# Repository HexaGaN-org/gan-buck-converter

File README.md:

# HexaGaN 48 V → 12 V GaN Synchronous Buck

A GaN-based synchronous buck converter with an onboard C2000 microcontroller, digital control and layered protections. HexaGaN's first in-house power PCB, built as a learning platform for the team and a rehearsal for the universal control board's power-stage interface.

> **Status (November 2026): tentative PCB layout, not ready for fabrication.** Circuitry on all six subsheets is captured and the root sheet is wired. The PCB has an outline and preliminary component placement, including XT30 input and XT60 output connectors, but placement, board-edge fit, power routing, and DRC still require substantial work. The two connectors currently overlap on the right edge and the `12V OUT` label is on the left; both need relocation and fit checks. The connector 3D models do not establish physical fit. On 2026-11-13, hierarchy ERC reported zero errors and six warnings; PCB DRC reported 770 violations and 362 unconnected items. The warnings and the [PWM overlap decision](docs/design/enable.md#open-questions) and [+5V handover margin](docs/design/input_supply.md#values-published-to-other-sheets) need review before layout freeze.

## At a glance

| | |
|---|---|
| Conversion | 48 V in → 12 V out, synchronous buck |
| Output | 12.5 A, 150 W design target; parts and copper rated for 200 W |
| Switching frequency | 400 kHz nominal, adjustable 300–500 kHz in firmware |
| Power stage | 2 × Infineon IGC033S10S1 GaN FETs, TI LM5113-Q1 gate driver |
| Controller | TI TMS320F280039C, 64-pin LQFP (same device as the universal control board) |
| Control | Staged bring-up: open loop → voltage mode → average current mode |
| Protections | Cycle-by-cycle overcurrent (CMPSS), output overvoltage, input undervoltage lockout, overtemperature, hardware enable, and static both-high PWM inhibit. Dynamic overlap protection is under review before layout freeze |
| Host interface | USB-C serial (CP2102N USB-UART bridge, ESD-protected) and a TI-compatible JTAG header |
| Assembly | JLCPCB Economic PCBA, single-sided |

Targets are in [docs/specifications.md](docs/specifications.md); each sheet's decisions and parts are in its design note in [docs/design/](docs/design/).

## Schematic sheets and owners

| # | Sheet | Owner | Status |
|---|---|---|---|
| 1 | Top (root sheet) | Reza Rahimzadeh | Wired: all six sheet symbols connected by their hierarchical pins. Four plated M3 mounting holes (H101–H104), pads on no net, a main-specifications block and a power tree |
| 2 | input_supply | Reza Rahimzadeh | Schematic complete: 48 V protection, input shunt, aux regulator, 5 V mux and 3.3 V LDO. Wired on the root sheet |
| 3 | power_stage | Reza Rahimzadeh | Captured, with reduced input and output capacitor banks (decision #24); wired on the root sheet |
| 4 | sensing | Connor Jin | Circuitry captured (six channels); labels aligned with the MCU sheet; wired on the root sheet |
| 5 | mcu | Yunxi He | Captured, with 16 MHz external crystal; all interface labels wired on the root sheet |
| 6 | enable | Connor Jin | Captured: watchdog, enable switch, `STAGE_EN` gating and static both-high inhibit. Dynamic overlap protection remains under review. Wired on the root sheet |
| 7 | comms_debug | Yunxi He | Captured: USB-C with CP2102N bridge and USBLC6 ESD protection, JTAG header. Wired on the root sheet |

The table uses each sheet's file name. On the root sheet the symbols carry display names (Input Supply, Power Stage, Sensing, Microcontroller, Enable, Comms and Debug).

Only a sheet's owner edits it. What each sheet contains and every signal that crosses between sheets are defined in [docs/schematic-hierarchy.md](docs/schematic-hierarchy.md).

## Repository layout

```
CONTRIBUTING.md              How we work: workflow, conventions, libraries, merge checklist
docs/
  specifications.md          Targets, limits and headline parts
  schematic-hierarchy.md     The contract between sheets: contents, signals, connectors
  design/                    One design note per sheet: decisions, calculations, parts, layout, tests
  guides/
    preferred-parts.md       JLCPCB passives to pick first, with measured DC-bias derating
    jlcpcb-assembly.md       Fab and assembly rules, ordering workflow, pre-order checklist
  firmware/
    firmware-requirements.md         Plain-language firmware guide for the firmware team
    edge-ai-dead-time-optimizer.md   Proposal: on-board model that picks the lowest-loss dead time and frequency
    pinmux-hardware.md              Physical MCU pin allocation frozen for PCB routing
  datasheets/                Datasheets, application notes and reference images the design notes link to
  block-diagram.svg          Board block diagram (edit the SVG directly when the architecture changes)
  gan-buck-converter-BOM.xlsx  Cost and notes per sheet, one row per unique part, rebuilt from the schematic
hardware/gan-buck-converter/
  gan-buck-converter.kicad_pro / .kicad_sch / .kicad_pcb   KiCad 10 project (root sheet and board)
  sheets/                    The six hierarchical sheets
  lib/                       hexagan library: hand-made symbols, footprints, 3D models (see lib/README.md)
  JLCImport.*                Parts imported from LCSC by the JLCImport plugin
simulations/
  voltage_mode_sim.py        Python model of the voltage-mode control loop: Bode plots, load step
  input_hotplug_sim.py       Input hot-plug ringing and damping, bulk-capacitor ripple, input-filter stability
  efficiency_estimate.py     Component loss budget and theoretical efficiency vs load, input voltage and frequency
  README.md                  How to run it, how to read the plots, what we've learned
```

Firmware source (C2000, SysConfig) will live in `firmware/` once that work starts.

## Contributing

Read [CONTRIBUTING.md](CONTRIBUTING.md) before your first commit: tool setup, the pull-and-push routine, schematic conventions, library rules and the checklist every sheet passes before it merges.

## Safety

48 V is below the 60 V DC SELV limit, but a shorted output or a failed switch can still deliver large currents and burn hardware.

- Always bring up from a **current-limited bench supply**, starting at reduced input voltage with no load.
- Connect J201 with the 48 V supply output **off**, then enable the supply. Do not routinely live-plug at 51 V until the revised input protection is measured; the controlled hot-plug test is in [input_supply.md](docs/design/input_supply.md#verification).
- Bring up the 5 V supply (through J202, the keyed external 5 V input, set to 5.0 V) before applying 48 V. J202 cuts off above about 5.2–5.7 V.
- Check polarity before connecting any electronic load or source. J201 is a male XT30 48 V input and J301 is a female XT60 12 V output; they require separate soldered adapter cables. 48 V on J301 destroys the output capacitors. See the [connector and harness instructions](docs/design/input-output-connectors.md).
- Use a 48 V supply whose **DC output floats from earth**; keep the supply's chassis protective earth connected. Set supply OVP near 55 V if available. Above about 57 V the input TVS conducts continuously.
- **Q201 grounding rule:** J201− is separate from board `GND`. Attach grounded scope clips only to board `GND`, never J201−. If both supply negative and board `GND` are earthed, USB/JTAG/scope wiring can carry input return current around Q201 during normal operation. Swapping the input leads alone does not create that bypass, but a fixed J201−-to-GND short defeats the reverse block. H101–H104 are plated but on no net: never connect them to `GND` or any other net, and keep other copper clear of their mounting hardware.
- **Grounded-scope design limit:** Moving reverse protection to the positive rail alone does not eliminate the supply/scope earth loop. If J201− were then tied directly to board `GND`, reversed leads with a grounded scope attached could short supply positive to earth outside F201. Use the [grounding and scope note](docs/design/input_supply.md#grounding-and-scope-measurements) before changing this topology or using a shared-ground source.
- The power stage stays disabled until the hardware enable is asserted. Firmware alone cannot enable it.

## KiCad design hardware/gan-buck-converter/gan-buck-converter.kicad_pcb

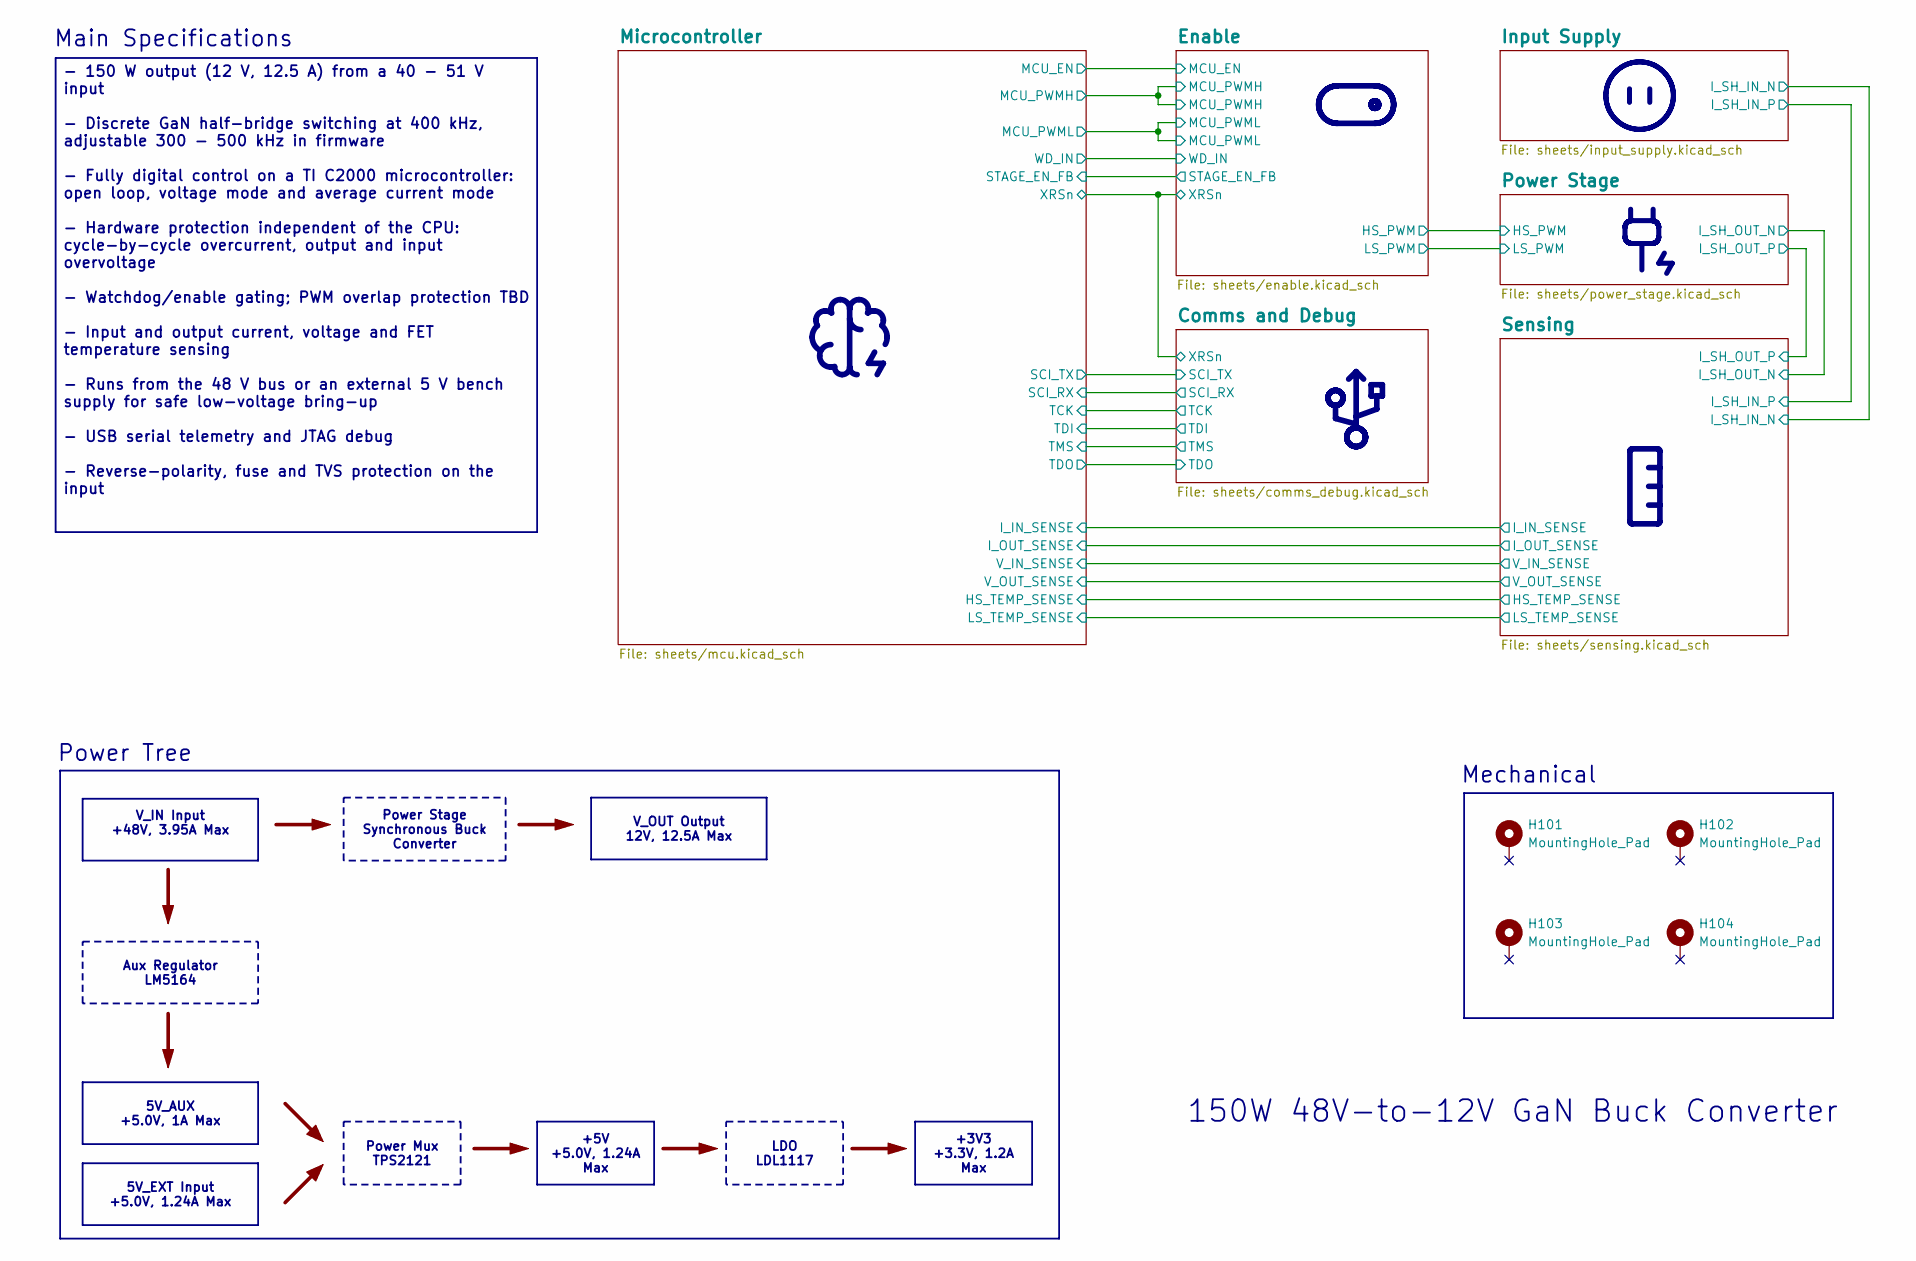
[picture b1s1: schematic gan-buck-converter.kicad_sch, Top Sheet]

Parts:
H101, H102, H103, H104: MountingHole_Pad; MountingHole_3.2mm_M3_Pad

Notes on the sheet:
Main Specifications
150W 48V-to-12V GaN Buck Converter
Power Tree
Mechanical
+3V3 +3.3V, 1.2A Max
- 150 W output (12 V, 12.5 A) from a 40 - 51 V input - Discrete GaN half-bridge switching at 400 kHz, adjustable 300 - 500 kHz in firmware - Fully digital control on a TI C2000 microcontroller: open loop, voltage mode and average current mode - Hardware protection independent of the CPU: cycle-by-c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
Power Mux TPS2121
V_OUT Output 12V, 12.5A Max
Power Stage Synchronous Buck Converter
V_IN Input +48V, 3.95A Max
Aux Regulator LM5164
5V_EXT Input +5.0V, 1.24A Max
LDO LDL1117
5V_AUX +5.0V, 1A Max
+5V +5.0V, 1.24A Max

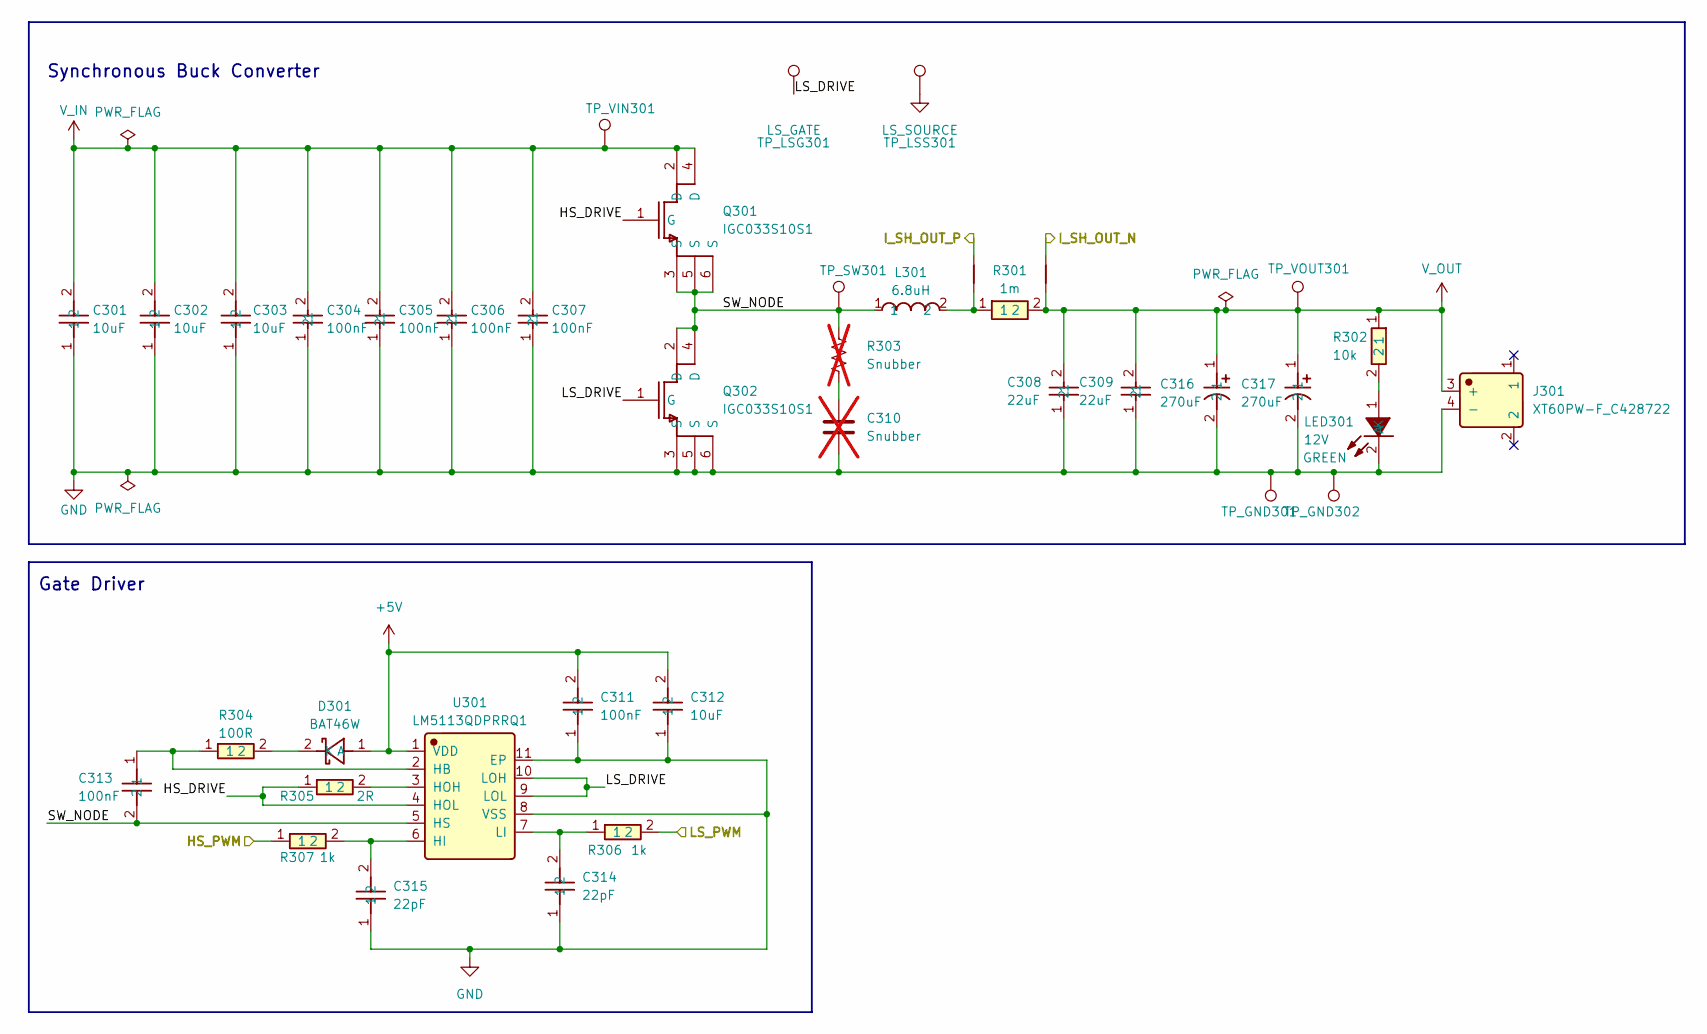
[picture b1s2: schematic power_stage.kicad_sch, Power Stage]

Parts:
C301, C302, C303: 10uF; C_1210_3225Metric; Manufacturer Part CL32Y106KCV6PNE; LCSC C22380050
C304, C305, C306, C307: 100nF; C_0603_1608Metric; Manufacturer Part CL10B104KC8NNNC; LCSC C15725
C308, C309: 22uF; C_1206_3216Metric_Pad1.33x1.80mm_HandSolder; Manufacturer Part CL31A226KAHNNNE; LCSC C12891
C310: Snubber; C_1206_3216Metric; not fitted
C311, C313: 100nF; CC0603KRX7R9BB104; Manufacturer Part CC0603KRX7R9BB104; LCSC C14663
C312: 10uF; CL10A106MA8NRNC; Manufacturer Part CL10A106MA8NRNC; LCSC C96446
C314, C315: 22pF; CL10C220JB8NNNC; Manufacturer Part CL10C220JB8NNNC; LCSC C1653
C316, C317: 270uF; APXJ160ARA271MF80J; Manufacturer Part APXJ160ARA271MF80J; LCSC C2944013
D301: BAT46W; BAT46W_C7420332; Manufacturer Part BAT46W; LCSC C7420332
J301: XT60PW-F_C428722; Manufacturer Part XT60PW-F; LCSC C428722
L301: 6.8uH; SLB2212P6R8MTT; Manufacturer Part SLB2212P6R8MTT; LCSC C2842794
LED301: 12V; 0805G_Green; Manufacturer Part KT-0805G; LCSC C2297
NT301, NT302: NetTie_2; NetTie-2_SMD_Pad0.5mm
Q301, Q302: IGC033S10S1; IGC033S10S1_C41381300; Manufacturer Part IGC033S10S1; LCSC C41381300
R301: 1m; R_2512_6332Metric_Pad1.40x3.35mm_HandSolder; Manufacturer Part FPM253WFR001TML; LCSC C7420016
R302: 10k; 0603WAF1002T5E; Manufacturer Part 0603WAF1002T5E; LCSC C25804
R303: Snubber; R_1206_3216Metric; not fitted
R304: 100R; 0603WAF1000T5E; Manufacturer Part 0603WAF1000T5E; LCSC C22775
R305: 2R; 0603WAF200KT5E; Manufacturer Part 0603WAF200KT5E; LCSC C22977
R306, R307: 1k; 0603WAF1001T5E; Manufacturer Part 0603WAF1001T5E; LCSC C21190
TP_GND301, TP_GND302: TestPoint; TestPoint_Pad_D2.0mm
TP_LSG301: LS_GATE; TestPoint_Pad_D1.0mm
TP_LSS301: LS_SOURCE; TestPoint_Pad_D1.0mm
TP_SW301: TestPoint; TestPoint_Pad_D2.0mm
TP_VIN301: TestPoint; TestPoint_Pad_D2.0mm
TP_VOUT301: TestPoint; TestPoint_Pad_D2.0mm
U301: LM5113QDPRRQ1; Manufacturer Part LM5113QDPRRQ1; LCSC C2677036

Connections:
+5V: C311.2, C312.2, D301.1 (A), U301.1 (VDD); also elsewhere on the board
/Enable/HS_PWM: R307.1; also elsewhere on the board
/Enable/LS_PWM: R306.2; also elsewhere on the board
/Power Stage/HS_DRIVE: Q301.1 (G), R305.1, U301.4 (HOL)
/Power Stage/I_SH_OUT_N: NT302.2; also elsewhere on the board
/Power Stage/I_SH_OUT_P: NT301.2; also elsewhere on the board
/Power Stage/LS_DRIVE: Q302.1 (G), TP_LSG301.1 (1_1), U301.9 (LOL), U301.10 (LOH)
/Power Stage/SW_NODE: C313.2, L301.1, Q301.3 (S), Q301.5 (S), Q301.6 (S), Q302.2 (D), Q302.4 (D), R303.1, TP_SW301.1 (1_1), U301.5 (HS)
GND: C301.1, C302.1, C303.1, C304.1, C305.1, C306.1, C307.1, C308.1, C309.1, C310.2, C311.1, C312.1, C314.1, C315.1, C316.2, C317.2, J301.4 (-), LED301.2 (K), Q302.3 (S), Q302.5 (S), Q302.6 (S), TP_GND301.1 (1_1), TP_GND302.1 (1_1), TP_LSS301.1 (1_1), U301.8 (VSS), U301.11 (EP); also elsewhere on the board
unnamed: C310.1, R303.2
unnamed: D301.2 (K), R304.2
unnamed: L301.2, NT301.1, R301.1
unnamed: LED301.1 (A), R302.2
unnamed: C313.1, R304.1, U301.2 (HB)
unnamed: C315.2, R307.2, U301.6 (HI)
unnamed: R305.2, U301.3 (HOH)
unnamed: C314.2, R306.1, U301.7 (LI)
V_IN: C301.2, C302.2, C303.2, C304.2, C305.2, C306.2, C307.2, Q301.2 (D), Q301.4 (D), TP_VIN301.1 (1_1); also elsewhere on the board
V_OUT: C308.2, C309.2, C316.1, C317.1, J301.3 (+), NT302.1, R301.2, R302.1, TP_VOUT301.1 (1_1); also elsewhere on the board

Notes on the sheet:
Synchronous Buck Converter
Gate Driver

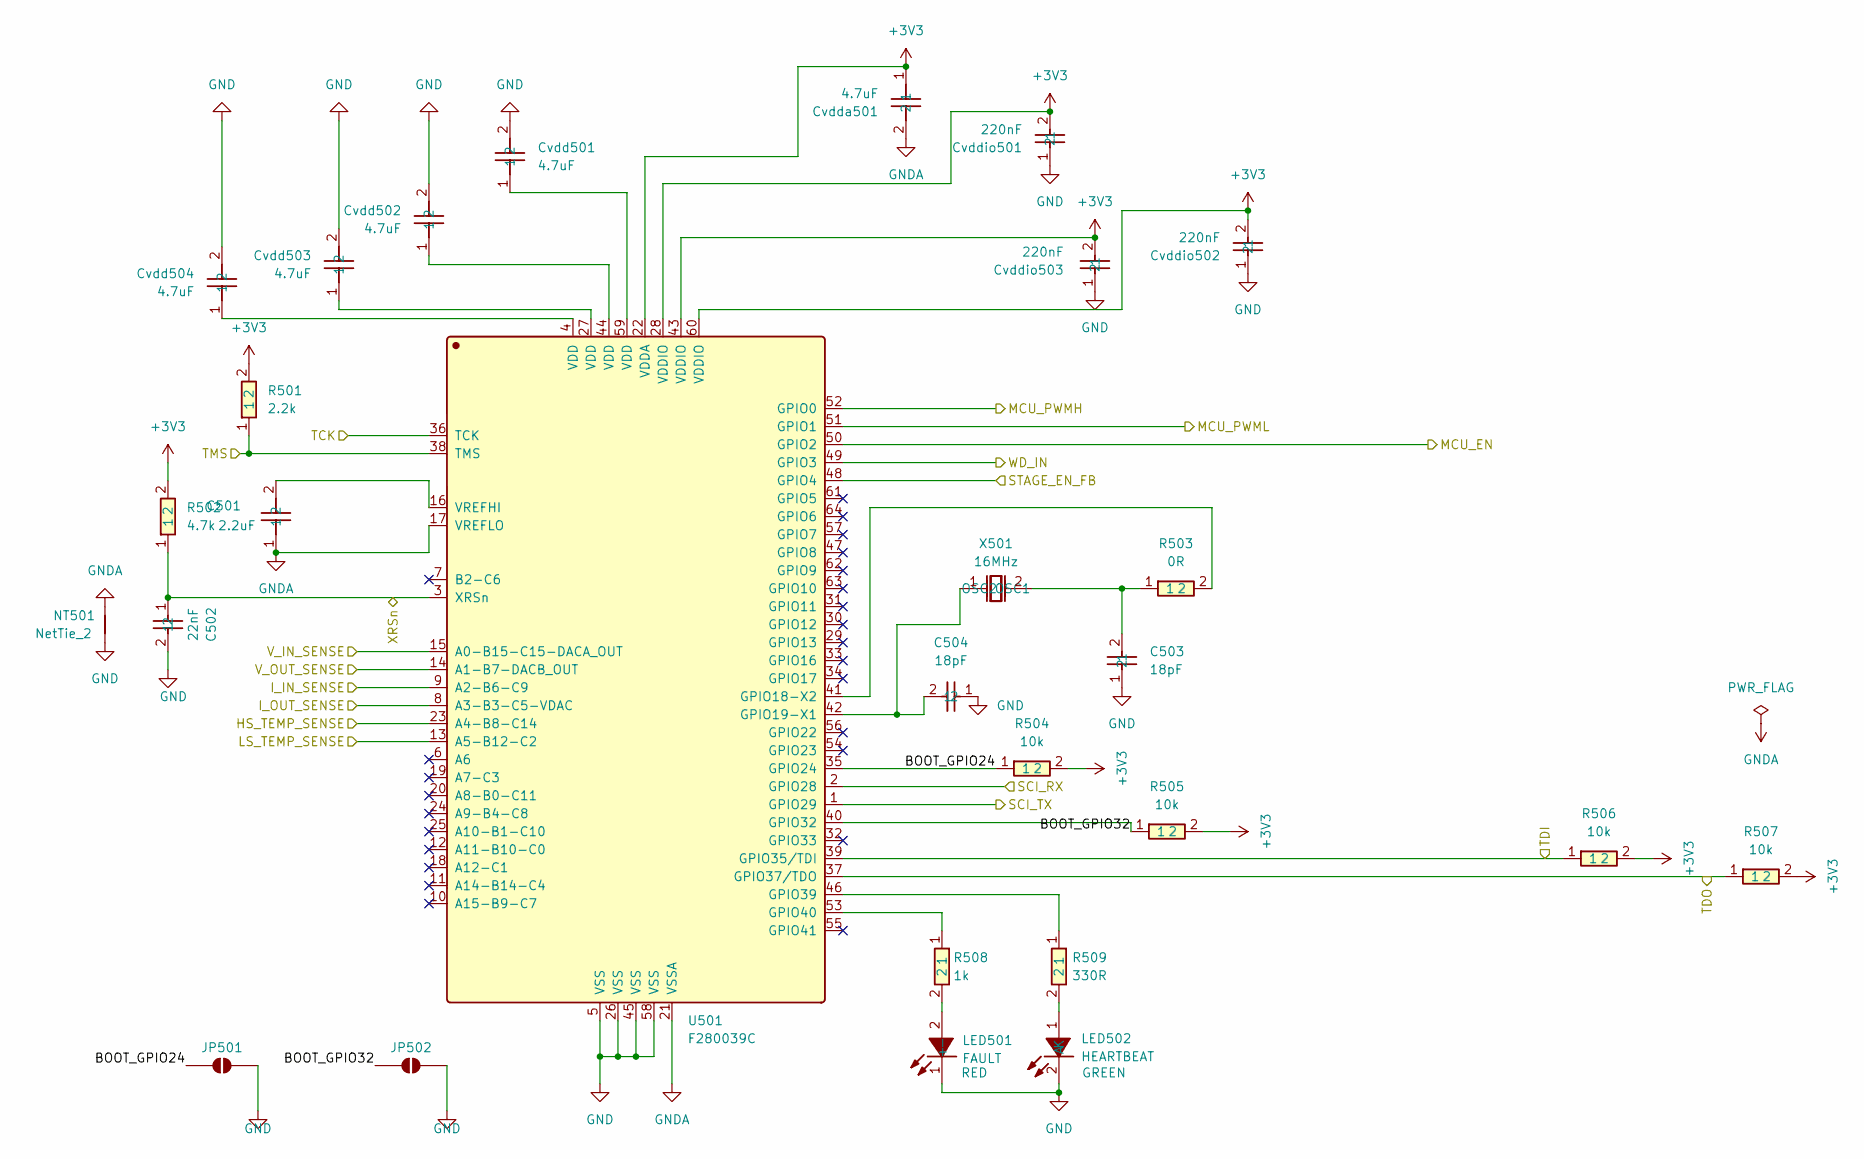
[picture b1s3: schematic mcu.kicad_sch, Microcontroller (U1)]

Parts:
C501: 2.2uF; GRM188R71A225KE15D; Manufacturer Part GRM188R71A225KE15D; LCSC C86018
C502: 22nF; CL10B223KB8NNNC; Manufacturer Part CL10B223KB8NNNC; LCSC C21122
C503, C504: 18pF; CL10C180JB8NNNC; Manufacturer Part CL10C180JB8NNNC; LCSC C1647
Cvdd501, Cvdd502, Cvdd503, Cvdd504: 4.7uF; CL10B475KQ8NQNC; Manufacturer Part CL10B475KQ8NQNC; LCSC C107368
Cvdda501: 4.7uF; CL10B475KQ8NQNC; Manufacturer Part CL10B475KQ8NQNC; LCSC C107368
Cvddio501, Cvddio502, Cvddio503: 220nF; CL10B224KA8NNNC; Manufacturer Part CL10B224KA8NNNC; LCSC C21120
JP501: BOOT_GPIO24; SolderJumper-2_P1.3mm_Open_Pad1.0x1.5mm
JP502: BOOT_GPIO32; SolderJumper-2_P1.3mm_Open_Pad1.0x1.5mm
LED501: FAULT; FC-2012HRK-620D; Manufacturer Part NCD0805R1; LCSC C84256
LED502: HEARTBEAT; 0805G_Green; Manufacturer Part KT-0805G; LCSC C2297
NT501: NetTie_2; NetTie-2_SMD_Pad0.5mm
R501: 2.2k; 0603WAF2201T5E; Manufacturer Part 0603WAF2201T5E; LCSC C4190
R502: 4.7k; RCT034K7JLF; Manufacturer Part RCT034K7JLF; LCSC C177333
R503: 0R; 0603WAJ0000T5E; Manufacturer Part 0603WAJ0000T5E; LCSC C15402
R504, R505, R506, R507: 10k; RCT0310KJLF; Manufacturer Part RCT0310KJLF; LCSC C177337
R508: 1k; 0603WAF1001T5E; Manufacturer Part 0603WAF1001T5E; LCSC C21190
R509: 330R; 0603WAF3300T5E; Manufacturer Part 0603WAF3300T5E; LCSC C23138
U501: F280039C; F280039CSPM; Manufacturer Part F280039CSPMR; LCSC C20345419
X501: 16MHz; ESD16_0000F12M25F; Manufacturer Part ESD16.0000F12M25F; LCSC C353726

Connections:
+3V3: Cvdda501.1, Cvddio501.2, Cvddio502.2, Cvddio503.2, R501.2, R502.2, R504.2, R505.2, R506.2, R507.2, U501.22 (VDDA), U501.28 (VDDIO), U501.43 (VDDIO), U501.60 (VDDIO); also elsewhere on the board
/Comms and Debug/SCI_RX: U501.2 (GPIO28); also elsewhere on the board
/Comms and Debug/SCI_TX: U501.1 (GPIO29); also elsewhere on the board
/Comms and Debug/TCK: U501.36 (TCK); also elsewhere on the board
/Comms and Debug/TDI: R506.1, U501.39 (GPIO35/TDI); also elsewhere on the board
/Comms and Debug/TDO: R507.1, U501.37 (GPIO37/TDO); also elsewhere on the board
/Comms and Debug/TMS: R501.1, U501.38 (TMS); also elsewhere on the board
/Comms and Debug/XRSn: C502.1, R502.1, U501.3 (XRSn); also elsewhere on the board
/Enable/MCU_EN: U501.50 (GPIO2); also elsewhere on the board
/Enable/MCU_PWMH: U501.52 (GPIO0); also elsewhere on the board
/Enable/MCU_PWML: U501.51 (GPIO1); also elsewhere on the board
/Enable/STAGE_EN_FB: U501.48 (GPIO4); also elsewhere on the board
/Enable/WD_IN: U501.49 (GPIO3); also elsewhere on the board
/Microcontroller/BOOT_GPIO24: JP501.1 (A), R504.1, U501.35 (GPIO24)
/Microcontroller/BOOT_GPIO32: JP502.1 (A), R505.1, U501.40 (GPIO32)
/Microcontroller/HS_TEMP_SENSE: U501.23 (A4-B8-C14); also elsewhere on the board
/Microcontroller/I_IN_SENSE: U501.9 (A2-B6-C9); also elsewhere on the board
/Microcontroller/I_OUT_SENSE: U501.8 (A3-B3-C5-VDAC); also elsewhere on the board
/Microcontroller/LS_TEMP_SENSE: U501.13 (A5-B12-C2); also elsewhere on the board
/Microcontroller/V_IN_SENSE: U501.15 (A0-B15-C15-DACA_OUT); also elsewhere on the board
/Microcontroller/V_OUT_SENSE: U501.14 (A1-B7-DACB_OUT); also elsewhere on the board
GND: C502.2, C503.1, C504.1, Cvdd501.2, Cvdd502.2, Cvdd503.2, Cvdd504.2, Cvddio501.1, Cvddio502.1, Cvddio503.1, JP501.2 (B), JP502.2 (B), LED501.1 (-), LED502.2 (K), NT501.1, U501.5 (VSS), U501.26 (VSS), U501.45 (VSS), U501.58 (VSS); also elsewhere on the board
GNDA: C501.1, Cvdda501.2, NT501.2, U501.17 (VREFLO), U501.21 (VSSA); also elsewhere on the board
unnamed: Cvdd501.1, U501.59 (VDD)
unnamed: Cvdd502.1, U501.44 (VDD)
unnamed: Cvdd503.1, U501.27 (VDD)
unnamed: Cvdd504.1, U501.4 (VDD)
unnamed: LED501.2 (+), R508.2
unnamed: LED502.1 (A), R509.2
unnamed: R503.2, U501.41 (GPIO18-X2)
unnamed: C504.2, U501.42 (GPIO19-X1), X501.1 (OSC1)
unnamed: R509.1, U501.46 (GPIO39)
unnamed: R508.1, U501.53 (GPIO40)
unnamed: C501.2, U501.16 (VREFHI)
unnamed: C503.2, R503.1, X501.2 (OSC2)

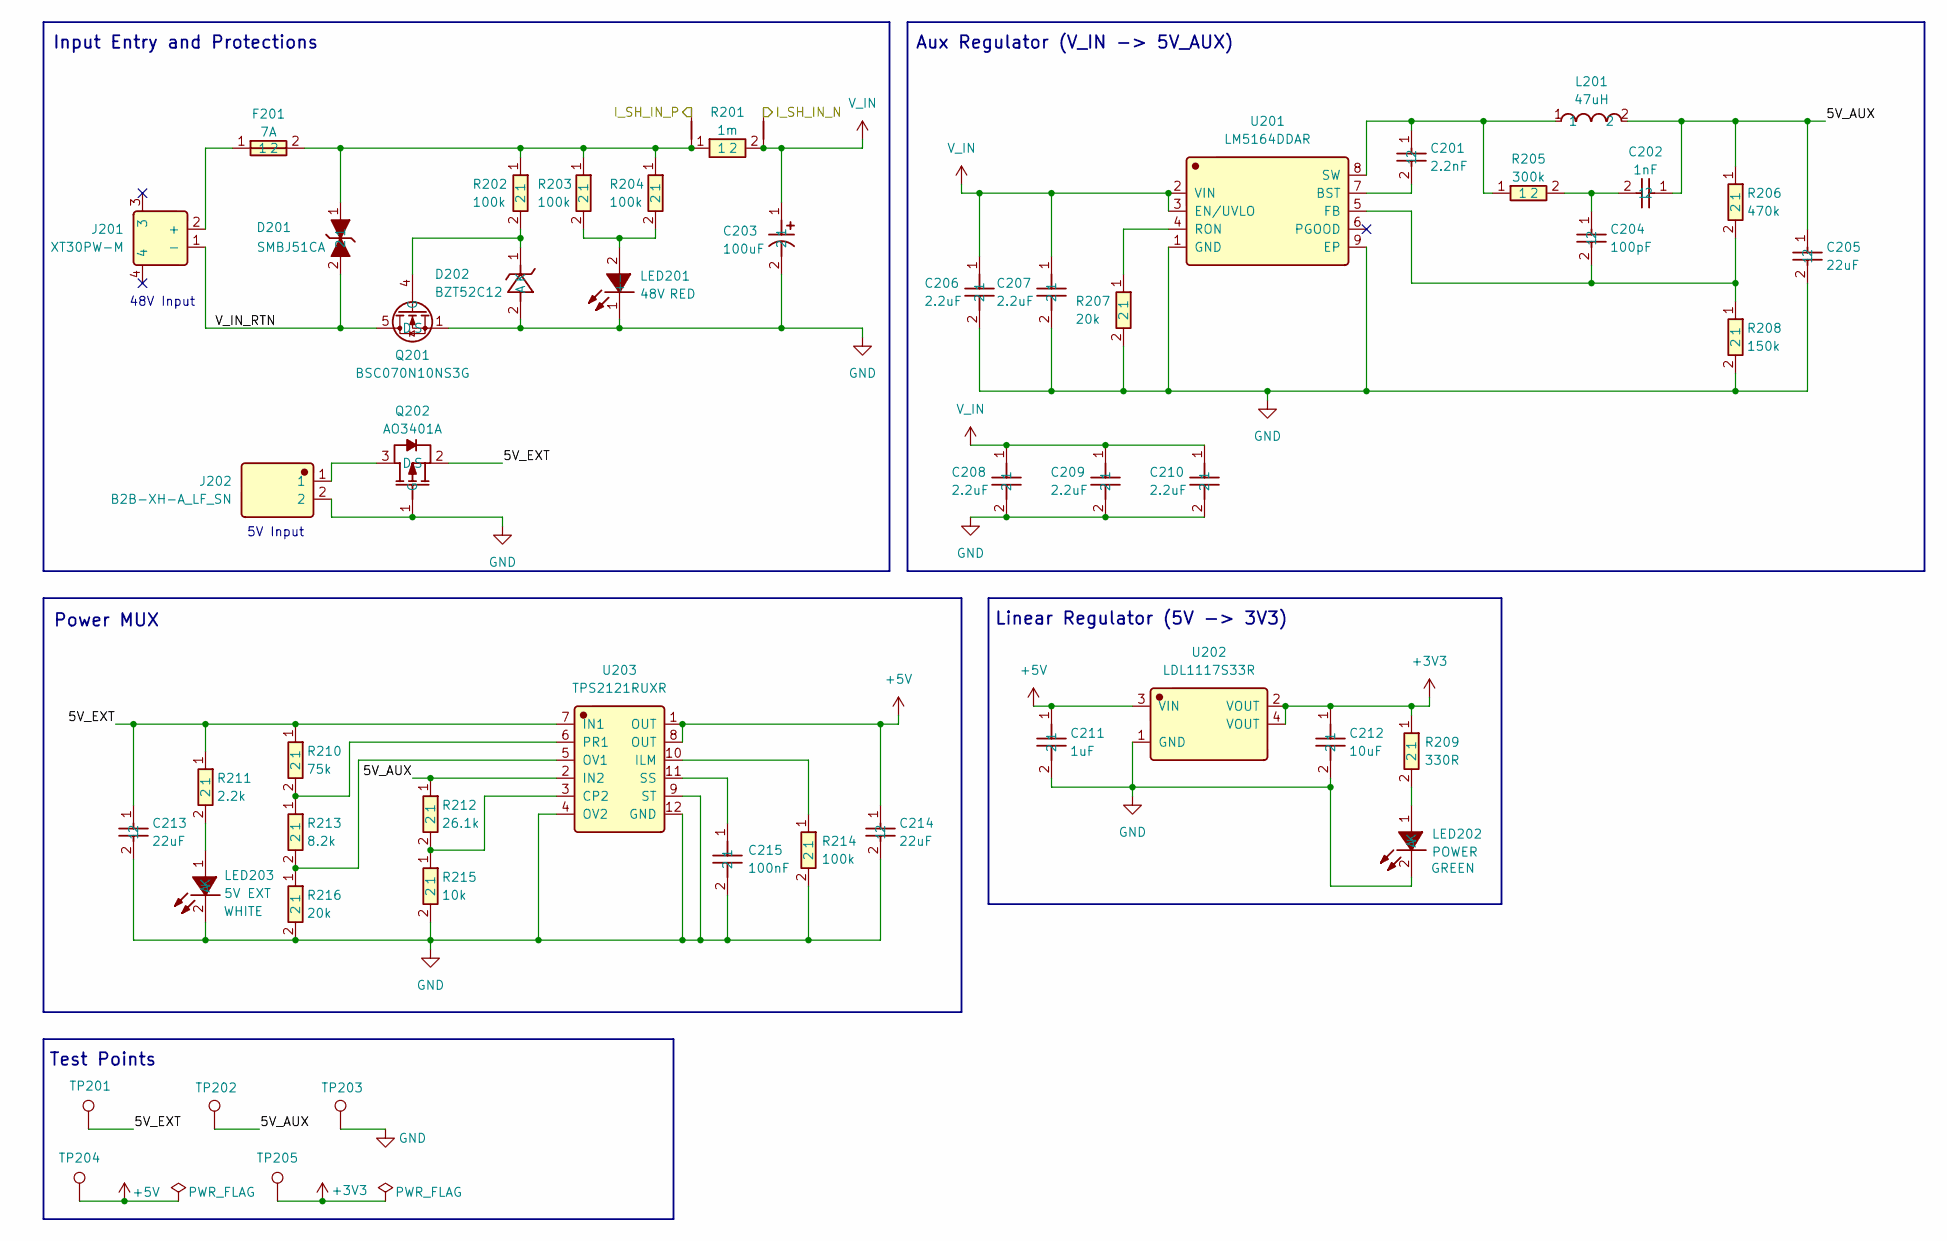
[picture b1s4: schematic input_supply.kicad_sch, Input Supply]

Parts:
C201: 2.2nF; 0603B222K500NT; Manufacturer Part 0603B222K500NT; LCSC C1604
C202: 1nF; CL10B102KB8NNNC; Manufacturer Part CL10B102KB8NNNC; LCSC C1588
C203: 100uF; VKME1452A101MV; Manufacturer Part VKME1452A101MV; LCSC C487440
C204: 100pF; CL10C101JB8NNNC; Manufacturer Part CL10C101JB8NNNC; LCSC C14858
C205, C213, C214: 22uF; C_1206_3216Metric_Pad1.33x1.80mm_HandSolder; Manufacturer Part CL31A226KAHNNNE; LCSC C12891
C206, C207, C208, C209, C210: 2.2uF; C_1206_3216Metric_Pad1.33x1.80mm_HandSolder; Manufacturer Part CL31B225KCHSNNE; LCSC C170101
C211: 1uF; CL10A105KB8NNNC; Manufacturer Part CL10A105KB8NNNC; LCSC C15849
C212: 10uF; CL10A106MA8NRNC; Manufacturer Part CL10A106MA8NRNC; LCSC C96446
C215: 100nF; CC0603KRX7R9BB104; Manufacturer Part CC0603KRX7R9BB104; LCSC C14663
D201: SMBJ51CA; SMBJ51CA_C41376101; Manufacturer Part SMBJ51CA; LCSC C41376101
D202: BZT52C12; D_SOD-123; Manufacturer Part BZT52C12; LCSC C19077410
F201: 7A; 0451007_MRL; Manufacturer Part 0451007.MRL; LCSC C99548
J201: XT30PW-M; Manufacturer Part XT30PW-M30.G.Y; LCSC C431092
J202: B2B-XH-A_LF_SN; Manufacturer Part B2B-XH-A(LF)(SN); LCSC C158012
L201: 47uH; FNR8040S470MT; Manufacturer Part FNR8040S470MT; LCSC C168137
LED201: 48V; FC-2012HRK-620D; Manufacturer Part NCD0805R1; LCSC C84256
LED202: POWER; 0805G_Green; Manufacturer Part KT-0805G; LCSC C2297
LED203: 5V EXT; whiteLEDSMD; Manufacturer Part KT-0805W; LCSC C34499
NT201, NT202: NetTie_2; NetTie-2_SMD_Pad0.5mm
Q201: BSC070N10NS3G; Manufacturer Part BSC070N10NS3G; LCSC C501502
Q202: AO3401A; Manufacturer Part AO3401A; LCSC C15127
R201: 1m; R_2512_6332Metric_Pad1.40x3.35mm_HandSolder; Manufacturer Part FPM253WFR001TML; LCSC C7420016
R202, R203, R204: 100k; R_1206_3216Metric; Manufacturer Part 1206W4F1003T5E; LCSC C17900
R205: 300k; R_0805_2012Metric_Pad1.20x1.40mm_HandSolder; Manufacturer Part 0805W8F3003T5E; LCSC C17616
R206: 470k; 0603WAF4703T5E; Manufacturer Part 0603WAF4703T5E; LCSC C23178
R207, R216: 20k; 0603WAF2002T5E; Manufacturer Part 0603WAF2002T5E; LCSC C4184
R208: 150k; 0603WAF1503T5E; Manufacturer Part 0603WAF1503T5E; LCSC C22807
R209: 330R; 0603WAF3300T5E; Manufacturer Part 0603WAF3300T5E; LCSC C23138
R210: 75k; 0603WAF7502T5E; Manufacturer Part 0603WAF7502T5E; LCSC C23242
R211: 2.2k; 0603WAF2201T5E; Manufacturer Part 0603WAF2201T5E; LCSC C4190
R212: 26.1k; 0603WAF2612T5E; Manufacturer Part 0603WAF2612T5E; LCSC C23356
R213: 8.2k; 0603WAF8201T5E; Manufacturer Part 0603WAF8201T5E; LCSC C25981
R214: 100k; 0603WAF1003T5E; Manufacturer Part 0603WAF1003T5E; LCSC C25803
R215: 10k; 0603WAF1002T5E; Manufacturer Part 0603WAF1002T5E; LCSC C25804
TP201: 5V_EXT; TestPoint_Pad_D2.0mm
TP202: 5V_AUX; TestPoint_Pad_D2.0mm
TP203: GND; TestPoint_Pad_D2.0mm
TP204: 5V; TestPoint_Pad_D2.0mm
TP205: 3V3; TestPoint_Pad_D2.0mm
U201: LM5164DDAR; Manufacturer Part LM5164DDAR; LCSC C477928
U202: LDL1117S33R; Manufacturer Part LDL1117S33R; LCSC C435835
U203: TPS2121RUXR; Texas_VQFN-HR-12_2x2.5mm_P0.5mm; Manufacturer Part TPS2121RUXR; LCSC C485916

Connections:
+3V3: C212.1, R209.1, TP205.1 (1_1), U202.2 (VOUT), U202.4 (VOUT); also elsewhere on the board
+5V: C211.1, C214.1, TP204.1 (1_1), U202.3 (VIN), U203.1 (OUT), U203.8 (OUT); also elsewhere on the board
/Input Supply/5V_AUX: C202.1, C205.1, L201.2, R206.1, R212.1, TP202.1 (1_1), U203.2 (IN2)
/Input Supply/5V_EXT: C213.1, Q202.2 (S), R210.1, R211.1, TP201.1 (1_1), U203.7 (IN1)
/Input Supply/I_SH_IN_N: NT202.2; also elsewhere on the board
/Input Supply/I_SH_IN_P: NT201.2; also elsewhere on the board
/Input Supply/V_IN_RTN: D201.2, J201.1 (-), Q201.5 (D), Q201.6 (D), Q201.7 (D), Q201.8 (D)
GND: C203.2, C205.2, C206.2, C207.2, C208.2, C209.2, C210.2, C211.2, C212.2, C213.2, C214.2, C215.2, D202.2 (A), J202.2, LED201.1 (-), LED202.2 (K), LED203.2 (K), Q201.1 (S), Q201.2 (S), Q201.3 (S), Q202.1 (G), R207.2, R208.2, R214.2, R215.2, R216.2, TP203.1 (1_1), U201.1 (GND), U201.9 (EP), U202.1 (GND), U203.4 (OV2), U203.9 (ST), U203.12 (GND); also elsewhere on the board
unnamed: C202.2, C204.1, R205.2
unnamed: D201.1, F201.2, NT201.1, R201.1, R202.1, R203.1, R204.1
unnamed: D202.1 (K), Q201.4 (G), R202.2
unnamed: F201.1, J201.2 (+)
unnamed: LED201.2 (+), R203.2, R204.2
unnamed: LED202.1 (A), R209.2
unnamed: LED203.1 (A), R211.2
unnamed: J202.1, Q202.3 (D)
unnamed: C201.2, U201.7 (BST)
unnamed: C204.2, R206.2, R208.1, U201.5 (FB)
unnamed: R207.1, U201.4 (RON)
unnamed: C201.1, L201.1, R205.1, U201.8 (SW)
unnamed: R212.2, R215.1, U203.3 (CP2)
unnamed: R214.1, U203.10 (ILM)
unnamed: R213.2, R216.1, U203.5 (OV1)
unnamed: R210.2, R213.1, U203.6 (PR1)
unnamed: C215.1, U203.11 (SS)
V_IN: C203.1, C206.1, C207.1, C208.1, C209.1, C210.1, NT202.1, R201.2, U201.2 (VIN), U201.3 (EN/UVLO); also elsewhere on the board

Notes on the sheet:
48V Input
Power MUX
Test Points
Aux Regulator (V_IN -> 5V_AUX)
Linear Regulator (5V -> 3V3)
Input Entry and Protections
5V Input

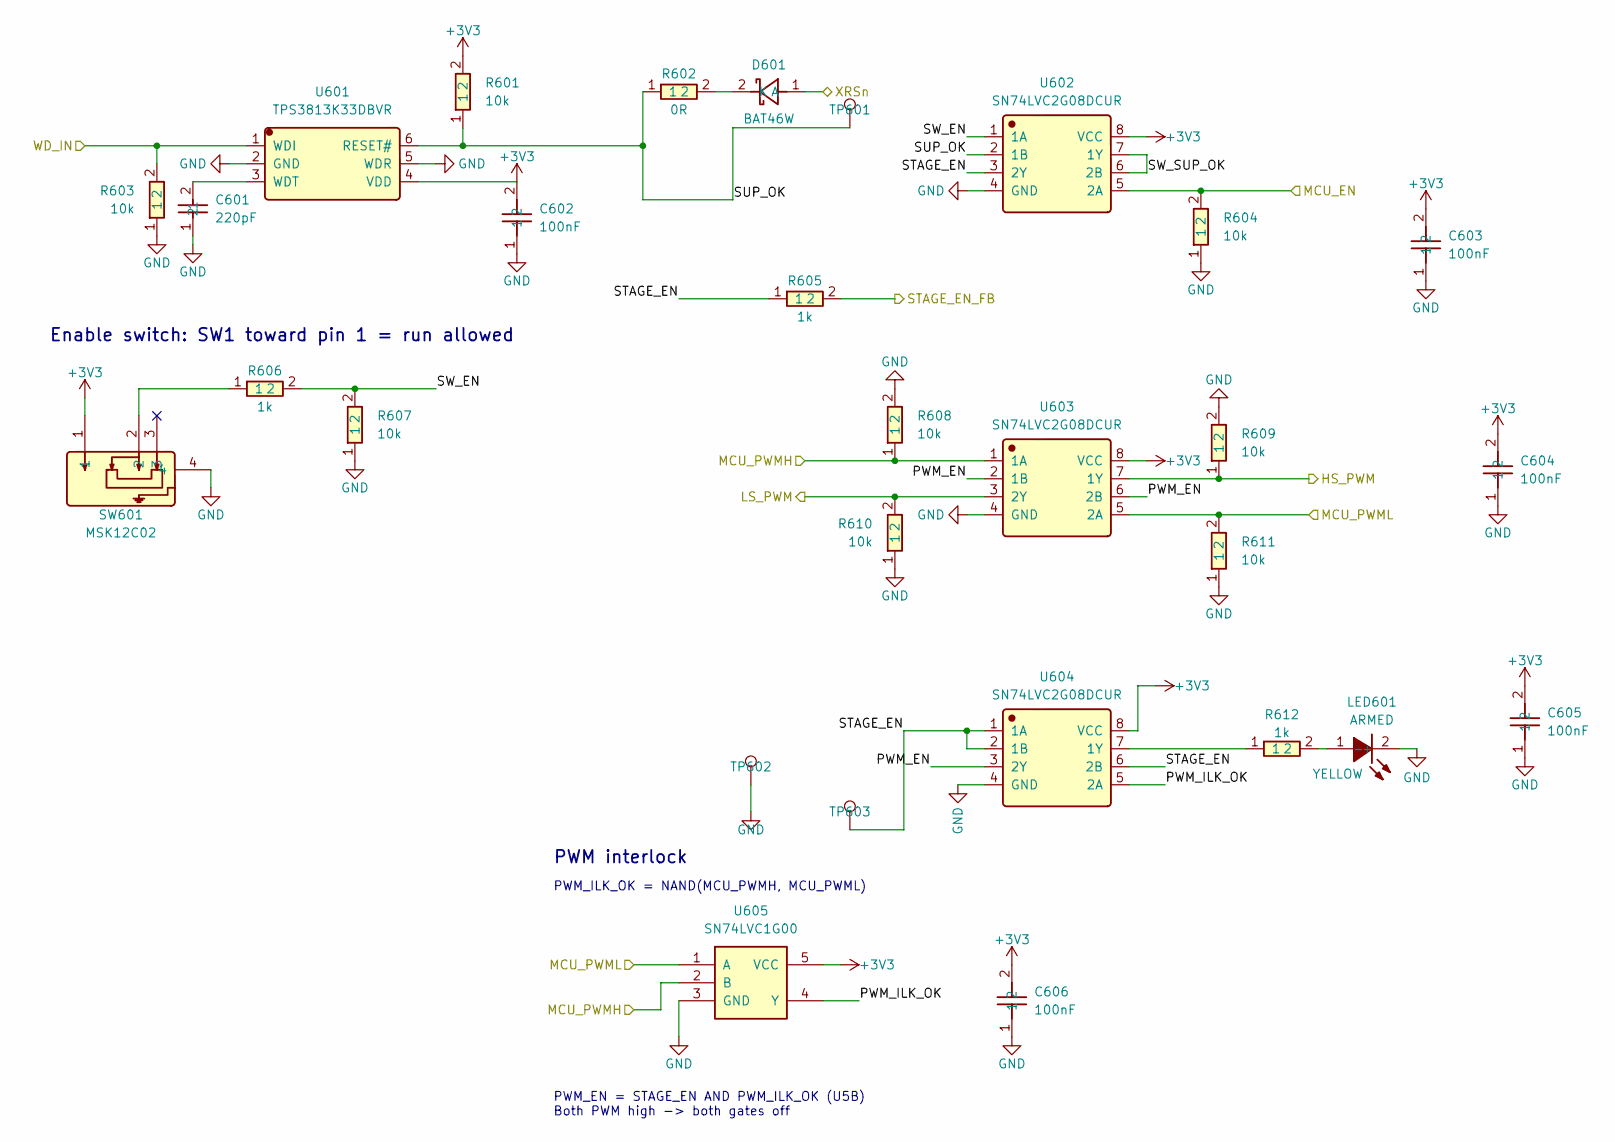
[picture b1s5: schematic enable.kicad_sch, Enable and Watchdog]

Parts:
C601: 220pF; CL10C221JB8NNNC; Manufacturer Part CL10C221JB8NNNC; LCSC C27675
C602, C603, C604, C605, C606: 100nF; CC0603KRX7R9BB104; Manufacturer Part CC0603KRX7R9BB104; LCSC C14663
D601: BAT46W; BAT46W_C7420332; Manufacturer Part BAT46W; LCSC C7420332
LED601: ARMED; 17-21SUYC_TR8; Manufacturer Part KT-0805Y; LCSC C2296
R601, R603, R604, R607, R608, R609, R610, R611: 10k; 0603WAF1002T5E; Manufacturer Part 0603WAF1002T5E; LCSC C25804
R602: 0R; 0603WAJ0000T5E; Manufacturer Part 0603WAJ0000T5E; LCSC C15402
R605, R606, R612: 1k; 0603WAF1001T5E; Manufacturer Part 0603WAF1001T5E; LCSC C21190
SW601: MSK12C02; Manufacturer Part MSK12C02; LCSC C431540
TP601: SUP_OK; TestPoint_Pad_D2.0mm
TP602: GND; TestPoint_Pad_D2.0mm
TP603: STAGE_EN; TestPoint_Pad_D2.0mm
U601: TPS3813K33DBVR; Manufacturer Part TPS3813K33DBVR; LCSC C93238
U602, U603, U604: SN74LVC2G08DCUR; Manufacturer Part SN74LVC2G08DCUR; LCSC C91875
U605: SN74LVC1G00; SN74LVC1G00DBVR; Manufacturer Part SN74LVC1G00DBVR; LCSC C7826

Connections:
+3V3: C602.2, C603.2, C604.2, C605.2, C606.2, R601.2, SW601.1, U601.4 (VDD), U602.8 (VCC), U603.8 (VCC), U604.8 (VCC), U605.5 (VCC); also elsewhere on the board
/Comms and Debug/XRSn: D601.1 (A); also elsewhere on the board
/Enable/HS_PWM: R609.1, U603.7 (1Y); also elsewhere on the board
/Enable/LS_PWM: R610.2, U603.3 (2Y); also elsewhere on the board
/Enable/MCU_EN: R604.2, U602.5 (2A); also elsewhere on the board
/Enable/MCU_PWMH: R608.1, U603.1 (1A), U605.2 (B); also elsewhere on the board
/Enable/MCU_PWML: R611.2, U603.5 (2A), U605.1 (A); also elsewhere on the board
/Enable/PWM_EN: U603.2 (1B), U603.6 (2B), U604.3 (2Y)
/Enable/PWM_ILK_OK: U604.5 (2A), U605.4 (Y)
/Enable/STAGE_EN: R605.1, TP603.1 (1_1), U602.3 (2Y), U604.1 (1A), U604.2 (1B), U604.6 (2B)
/Enable/STAGE_EN_FB: R605.2; also elsewhere on the board
/Enable/SUP_OK: R601.1, R602.1, TP601.1 (1_1), U601.6 (RESET#), U602.2 (1B)
/Enable/SW_EN: R606.2, R607.2, U602.1 (1A)
/Enable/SW_SUP_OK: U602.6 (2B), U602.7 (1Y)
/Enable/WD_IN: R603.2, U601.1 (WDI); also elsewhere on the board
GND: C601.1, C602.1, C603.1, C604.1, C605.1, C606.1, LED601.2 (-), R603.1, R604.1, R607.1, R608.2, R609.2, R610.1, R611.1, SW601.4, TP602.1 (1_1), U601.2 (GND), U601.5 (WDR), U602.4 (GND), U603.4 (GND), U604.4 (GND), U605.3 (GND); also elsewhere on the board
unnamed: D601.2 (K), R602.2
unnamed: LED601.1 (+), R612.2
unnamed: R606.1, SW601.2
unnamed: C601.2, U601.3 (WDT)
unnamed: R612.1, U604.7 (1Y)

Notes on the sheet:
Enable switch: SW1 toward pin 1 = run allowed
PWM interlock
PWM_ILK_OK = NAND(MCU_PWMH, MCU_PWML)
PWM_EN = STAGE_EN AND PWM_ILK_OK (U5B) Both PWM high -> both gates off
